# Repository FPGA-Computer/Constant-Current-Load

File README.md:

## Current Current Load
This is a constant current load useful for a maximum of 50V or 5A or 30W under forced air cooling. A MOSFET with a better package and improve cooling could improve on the upper power limit.

The opamp circuit is powered by an external 12V DC supply. The output current can be set by a 0-0.5V control signal.  The 0.1R 5W power resistor is used with an opamp feedabck loop.

The circuit is constructed on a single side PCB with a mix of SMT and through hole components.  The 10-pin connector is used for controlling and sensing the output.

A low Temperature coefficient sensing resistor with a noninverting amplifier is used for reading the current. It is roughly 0.5V/A intended for a 3.3V microcontroller.  The output gain can be changed by varying R6.

The PCB is mounted onto a 50W heatsink with MOSFET and a fan with a speed controller.

## Fan speed controller

I have a large bag of 10K thermistors (NTC MF52AT B3950) from aliexpress. The resistance vs temperature is similar to [Fenwal 10K Curve 16](http://techlib.com/electronics/thermistor_data.htm) 

The fan speed controller is a simple linear regulator with a thermistor and a resistor dividor for the voltage feedback. The fan reaches full speed around 45C. The 15K needs to be adjust for a thermistor Beta values other than 3950.

V(fan) = 2.5V * (Rth + 15K)/Rth.

I really needed a stud mounted part (3D printers) to sense the heatsink temperature, so I made my own.

I filed a hexagon hole in the PCB for a 4-40 hex jackscrew (commonly used for D-sub connectors).

The jackscrew is press fit (or hammered in my case) onto the PCB. The controller PCB is mounted flush onto the heatsink with the base of the stud making good thermal contact. 

I dipped the thermistor in thermal paste and fits into the screw hole. Hot gule or epoxy can then be applied to cover the sensor.  A small piece of PCB (~1cm^2) acts as the heatsink for the transistor.

License: 

Hardware - CC-BY 4.0

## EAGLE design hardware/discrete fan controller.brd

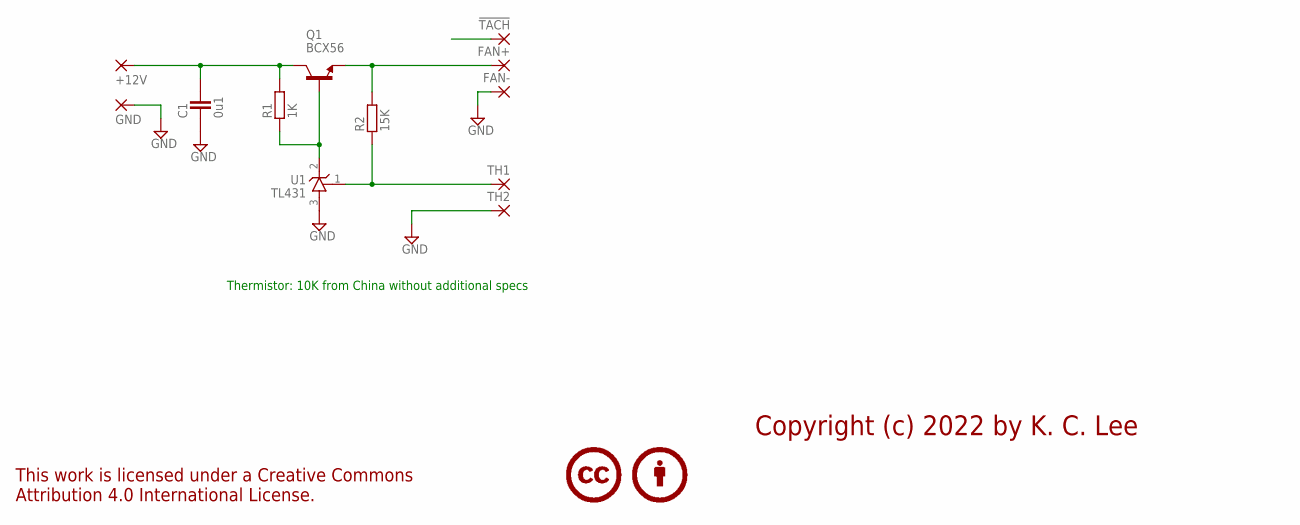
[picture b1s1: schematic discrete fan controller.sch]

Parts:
!TACH: SMD2; SMD1,27-2,54
+12V: SMD2; SMD1,27-2,54
C1: 0u1; CAPC2012X145AN
FAN+: SMD2; SMD1,27-2,54
FAN-: SMD2; SMD1,27-2,54
GND: SMD2; SMD1,27-2,54
LICENSE1: CC-BY50%; CC-BY-50
Q1: BCX56; SOT89
R1: 1K; RESC1608X55N
R2: 15K; RESC1608X55N
TH1, TH2: SMD2; SMD1,27-2,54
U1: TL431; SOT95P280X135-3N

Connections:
!TACH: !TACH.1
FAN+: FAN+.1, Q1.3 (E), R2.2
GND: C1.1, FAN-.1, GND.1, TH2.1, U1.3 (A)
unnamed: Q1.1 (B), R1.1, U1.2 (C)
unnamed: R2.1, TH1.1, U1.1 (R)
VCC: +12V.1, C1.2, Q1.2 (C), Q1.4 (C), R1.2

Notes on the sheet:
Thermistor: 10K from China without additional specs
Copyright (c) 2022 by K. C. Lee

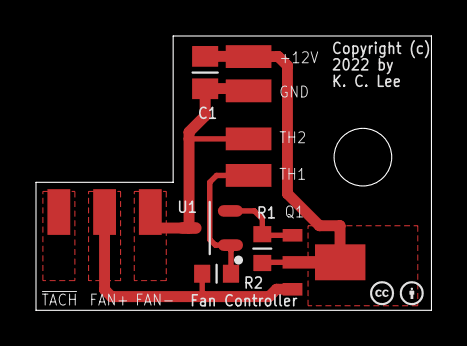
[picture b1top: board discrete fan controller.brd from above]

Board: 2 copper layers, 22.0 x 15.2 mm, 13 parts (0 on the bottom side), 5 nets.

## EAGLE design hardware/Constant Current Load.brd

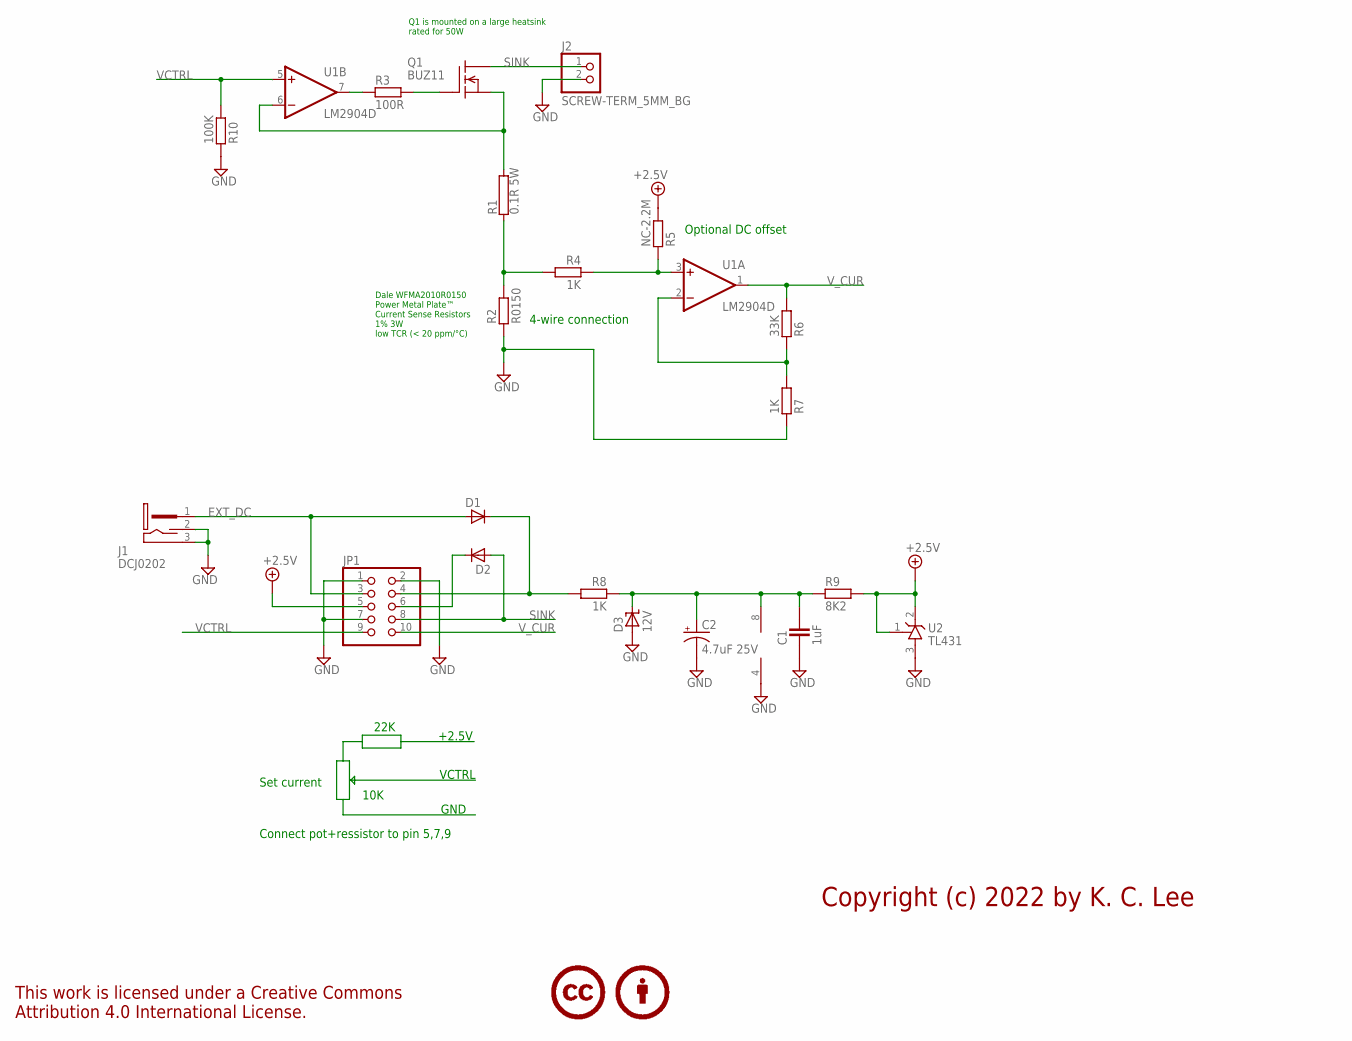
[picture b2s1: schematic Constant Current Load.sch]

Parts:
C1: 1uF; CAPC1608X92N
C2: 4.7uF 25V; E5-6
D1, D2: DIODE_SOT-23; SOT95P280X135-3N
D3: 12V; SOT95P280X135-3N
J1: DCJ0202; DCJ0202-SLOTTED
J2: SCREW-TERM_5MM_BG; 1X02-5MM-BG
JP1: PINHD-2X5_2.54-W/PLUG; 2X05-W_PLUG
LICENSE1: CC-BY50%; CC-BY-50
Q1: BUZ11; TO220
R1: 0.1R 5W; HPS923
R2: R0150; RESC5025X70N
R3: 100R; RESC2012X70N
R4, R7: 1K; RESC1608X55N
R5: NC-2.2M; RESC1608X55N
R6: 33K; RESC1608X55N
R8: 1K; RESC2012X70N
R9: 8K2; RESC2012X70N
R10: 100K; RESC1608X55N
U1: LM2904D; SO08
U2: TL431; SOT95P280X135-3N

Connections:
+2.5V: JP1.5, R5.2, R9.2, U2.1 (R), U2.2 (C)
EXT_DC: D1.1 (A), J1.1, JP1.3
GND: C1.1, C2.-, D3.1 (A), J1.2, J1.3, J2.2, JP1.1, JP1.2, JP1.7, R2.1, R7.1, R10.1, U1.4 (V-), U2.3 (A)
unnamed: Q1.3 (S), R1.2, U1.6 (-IN)
unnamed: C1.2, C2.+, D3.3 (K), R8.1, R9.1, U1.8 (V+)
unnamed: D2.3 (K), JP1.6
unnamed: Q1.1 (G), R3.2
unnamed: R3.1, U1.7 (OUT)
unnamed: R1.1, R2.2, R4.2
unnamed: R4.1, R5.1, U1.3 (+IN)
unnamed: R6.1, R7.2, U1.2 (-IN)
SINK: D2.1 (A), J2.1, JP1.8, Q1.2 (D)
VCTRL: JP1.9, R10.2, U1.5 (+IN)
V_BUS: D1.3 (K), JP1.4, R8.2
V_CUR: JP1.10, R6.2, U1.1 (OUT)

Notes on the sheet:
4-wire connection
Optional DC offset
Connect pot+ressistor to pin 5,7,9
+2.5V
GND
VCTRL
Set current
Dale WFMA2010R0150 Power Metal Plate™ Current Sense Resistors 1% 3W low TCR (< 20 ppm/°C)
22K
10K
Copyright (c) 2022 by K. C. Lee
Q1 is mounted on a large heatsink rated for 50W

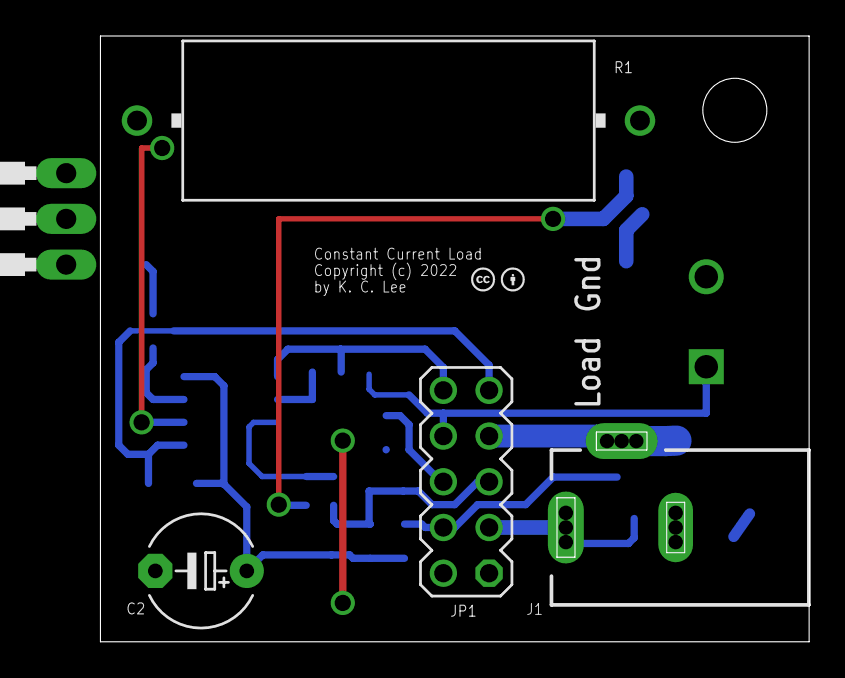
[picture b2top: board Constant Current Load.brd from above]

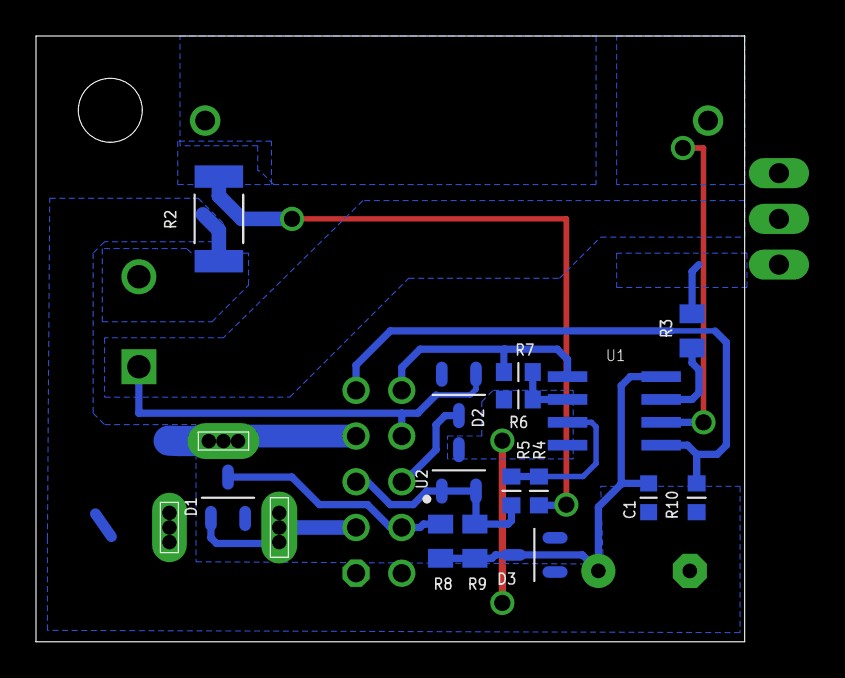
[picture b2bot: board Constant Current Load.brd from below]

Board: 2 copper layers, 39.4 x 33.7 mm, 22 parts (15 on the bottom side), 15 nets.

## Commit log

2022-06-01 Initial release
2022-06-08 Power figure revised
    Theta JC for MOSFET is high at 1.67C/W which limits power dissipation
2022-06-16 Added fan speed controller
2022-06-18 Add fan curve, file name changes
2022-12-26 TL431 Minimum current
    4K7 changed to 1K.

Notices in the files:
parts and their libraries:
Misc logo: This work is licensed under a Creative Commons
Attribution 4.0 International License.
